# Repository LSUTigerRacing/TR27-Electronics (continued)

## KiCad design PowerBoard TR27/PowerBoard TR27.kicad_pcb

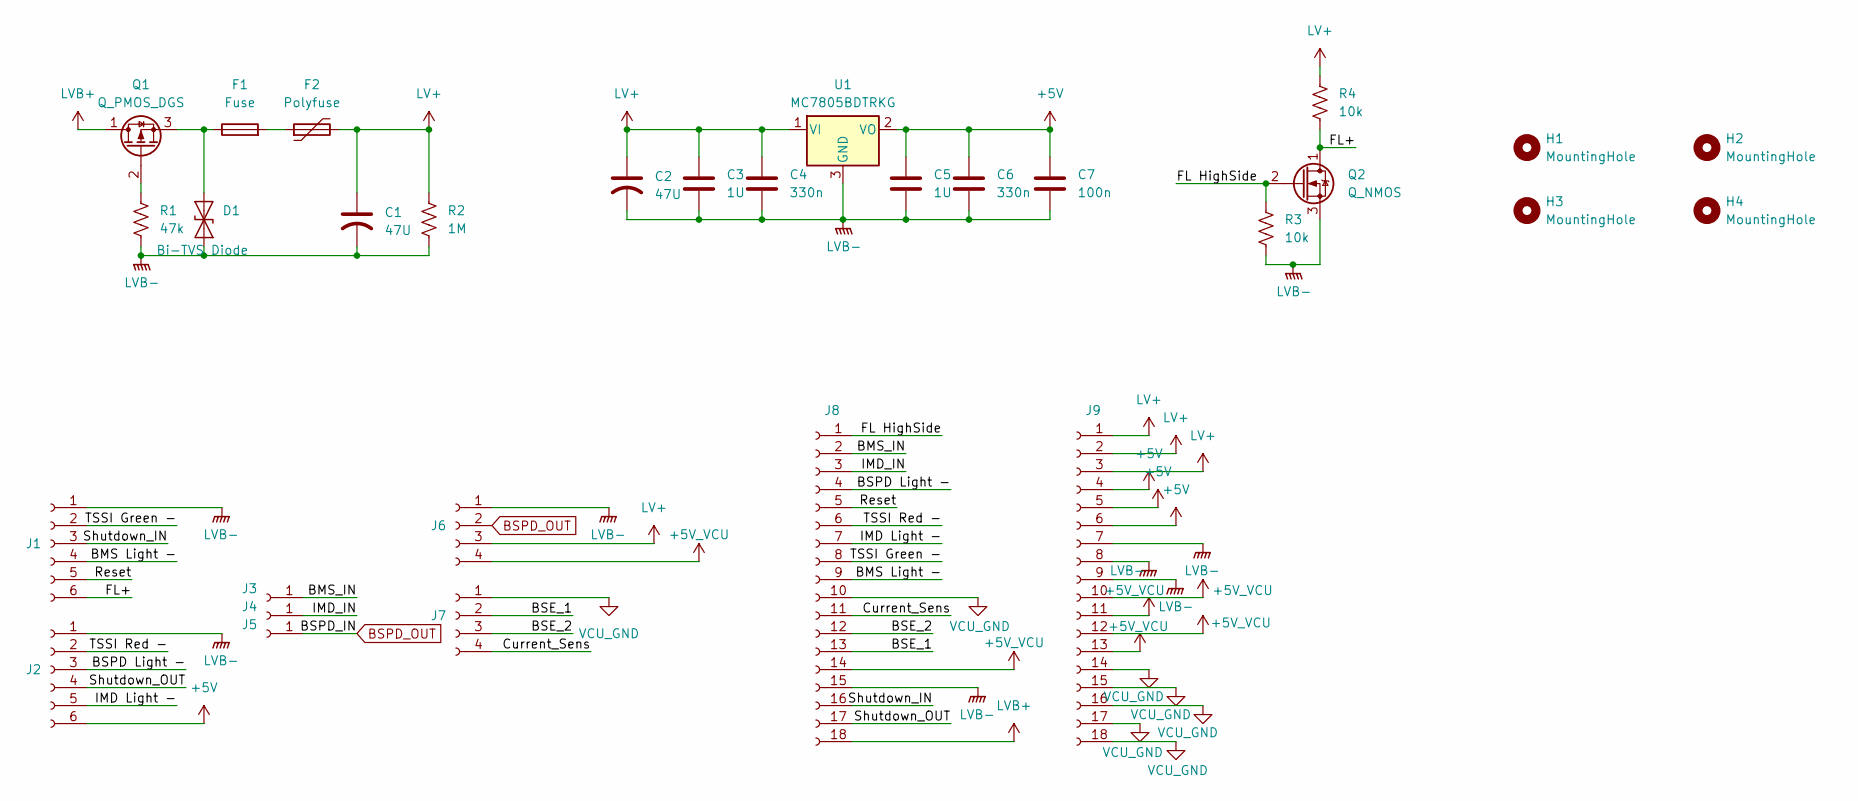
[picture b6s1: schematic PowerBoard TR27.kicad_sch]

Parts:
C1, C2: 47U; CP_Elec_6.3x5.4; JLC# C2836440
C3, C5: 1U; C_0603_1608Metric
C4, C6: 330n; C_0603_1608Metric
C7: 100n; C_0603_1608Metric
D1: Bi-TVS Diode; D_SOD-523; Mouser# 750-CPDUR12V-HF; JLC# C2443698
F1: Fuse; Fuseholder_Blade_Mini_Keystone_3568
F2: Polyfuse; R_0805_2012Metric
H1, H2, H3, H4: MountingHole; MountingHole_3.2mm_M3_DIN965_Pad
J1, J2: Conn_01x06_Socket; SAMTEC-CES-103-01-X-D
J3, J4, J5: Conn_01x01_Socket; SAMTEC_CES-101-01-T-S
J6, J7: Conn_01x04_Socket; SAMTEC_CES-104-X-X-S
J8, J9: Conn_01x18_Socket; CONN_SD-43045-001_18_MOL
Q1: Q_PMOS_DGS; SOT-23-3
Q2: Q_NMOS; SOT-23-3
R1: 47k; R_0805_2012Metric
R2: 1M; R_0805_2012Metric
R3, R4: 10k; R_0805_2012Metric
U1: MC7805BDTRKG; TO-252-3_TabPin2

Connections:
+5V: C5.1, C6.1, C7.1, J2.6, J9.4, J9.5, J9.6, U1.2 (VO)
+5V_VCU: J6.4, J8.14, J9.10, J9.11, J9.12, J9.13
/BMS Light -: J1.4, J8.9
/BMS_IN: J3.1 (Pin_1_1), J8.2
/BSE_1: J7.2, J8.13
/BSE_2: J7.3, J8.12
/BSPD Light -: J2.3, J8.4
/Current_Sens: J7.4, J8.11
/FL HighSide: J8.1, Q2.2 (G), R3.1
/FL+: J1.6, Q2.1 (D), R4.2
/IMD Light -: J2.5, J8.7
/IMD_IN: J4.1 (Pin_1_1), J8.3
/Reset: J1.5, J8.5
/Shutdown_IN: J1.3, J8.16
/Shutdown_OUT: J2.4, J8.17
/TSSI Green -: J1.2, J8.8
/TSSI Red -: J2.2, J8.6
BSPD_OUT: J5.1 (Pin_1_1), J6.2
LV+: C1.1, C2.1, C3.1, C4.1, F2.2, J6.3, J9.1, J9.2, J9.3, R2.1, R4.1, U1.1 (VI)
LVB+: J8.18, Q1.1 (D)
LVB-: C1.2, C2.2, C3.2, C4.2, C5.2, C6.2, C7.2, D1.1 (A1), J1.1, J2.1, J6.1, J8.15, J9.7, J9.8, J9.9, Q2.3 (S), R1.2, R2.2, R3.2, U1.3 (GND)
unnamed: D1.2 (A2), F1.1, Q1.3 (S)
unnamed: F1.2, F2.1
unnamed: Q1.2 (G), R1.1
VCU_GND: J7.1, J8.10, J9.14, J9.15, J9.16, J9.17, J9.18

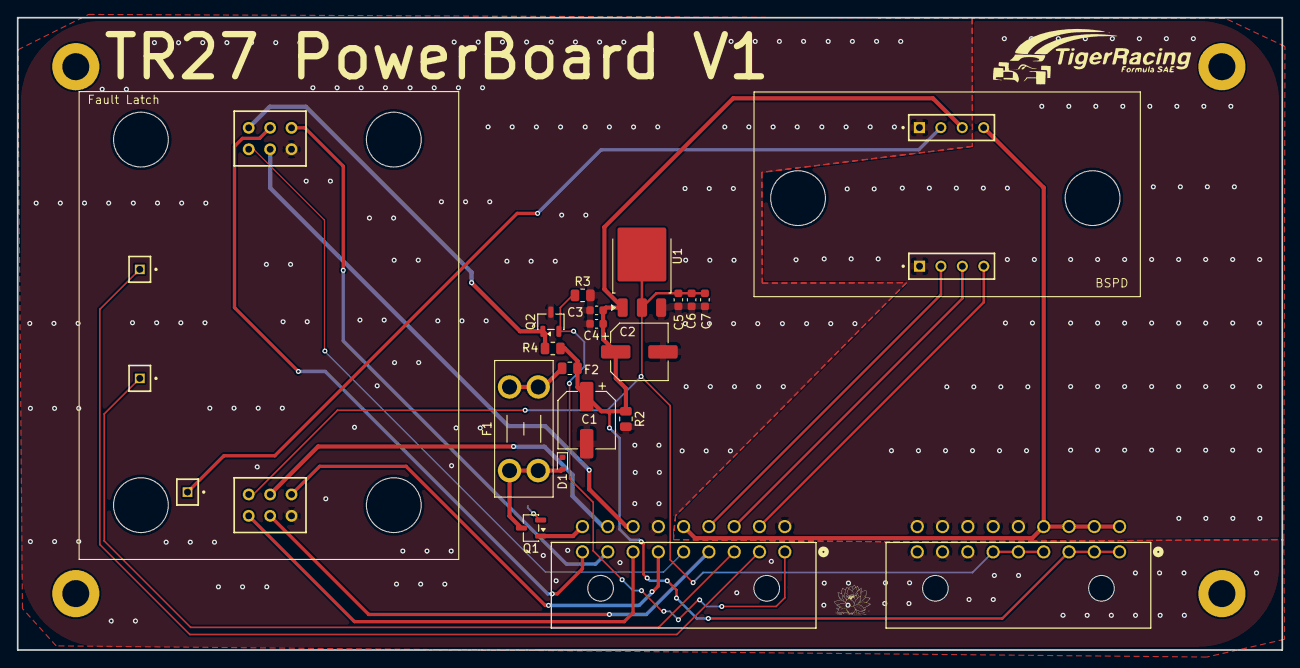
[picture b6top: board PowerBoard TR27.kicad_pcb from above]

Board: 2 copper layers, 150.0 x 75.0 mm, 30 parts (1 on the bottom side), 25 nets.

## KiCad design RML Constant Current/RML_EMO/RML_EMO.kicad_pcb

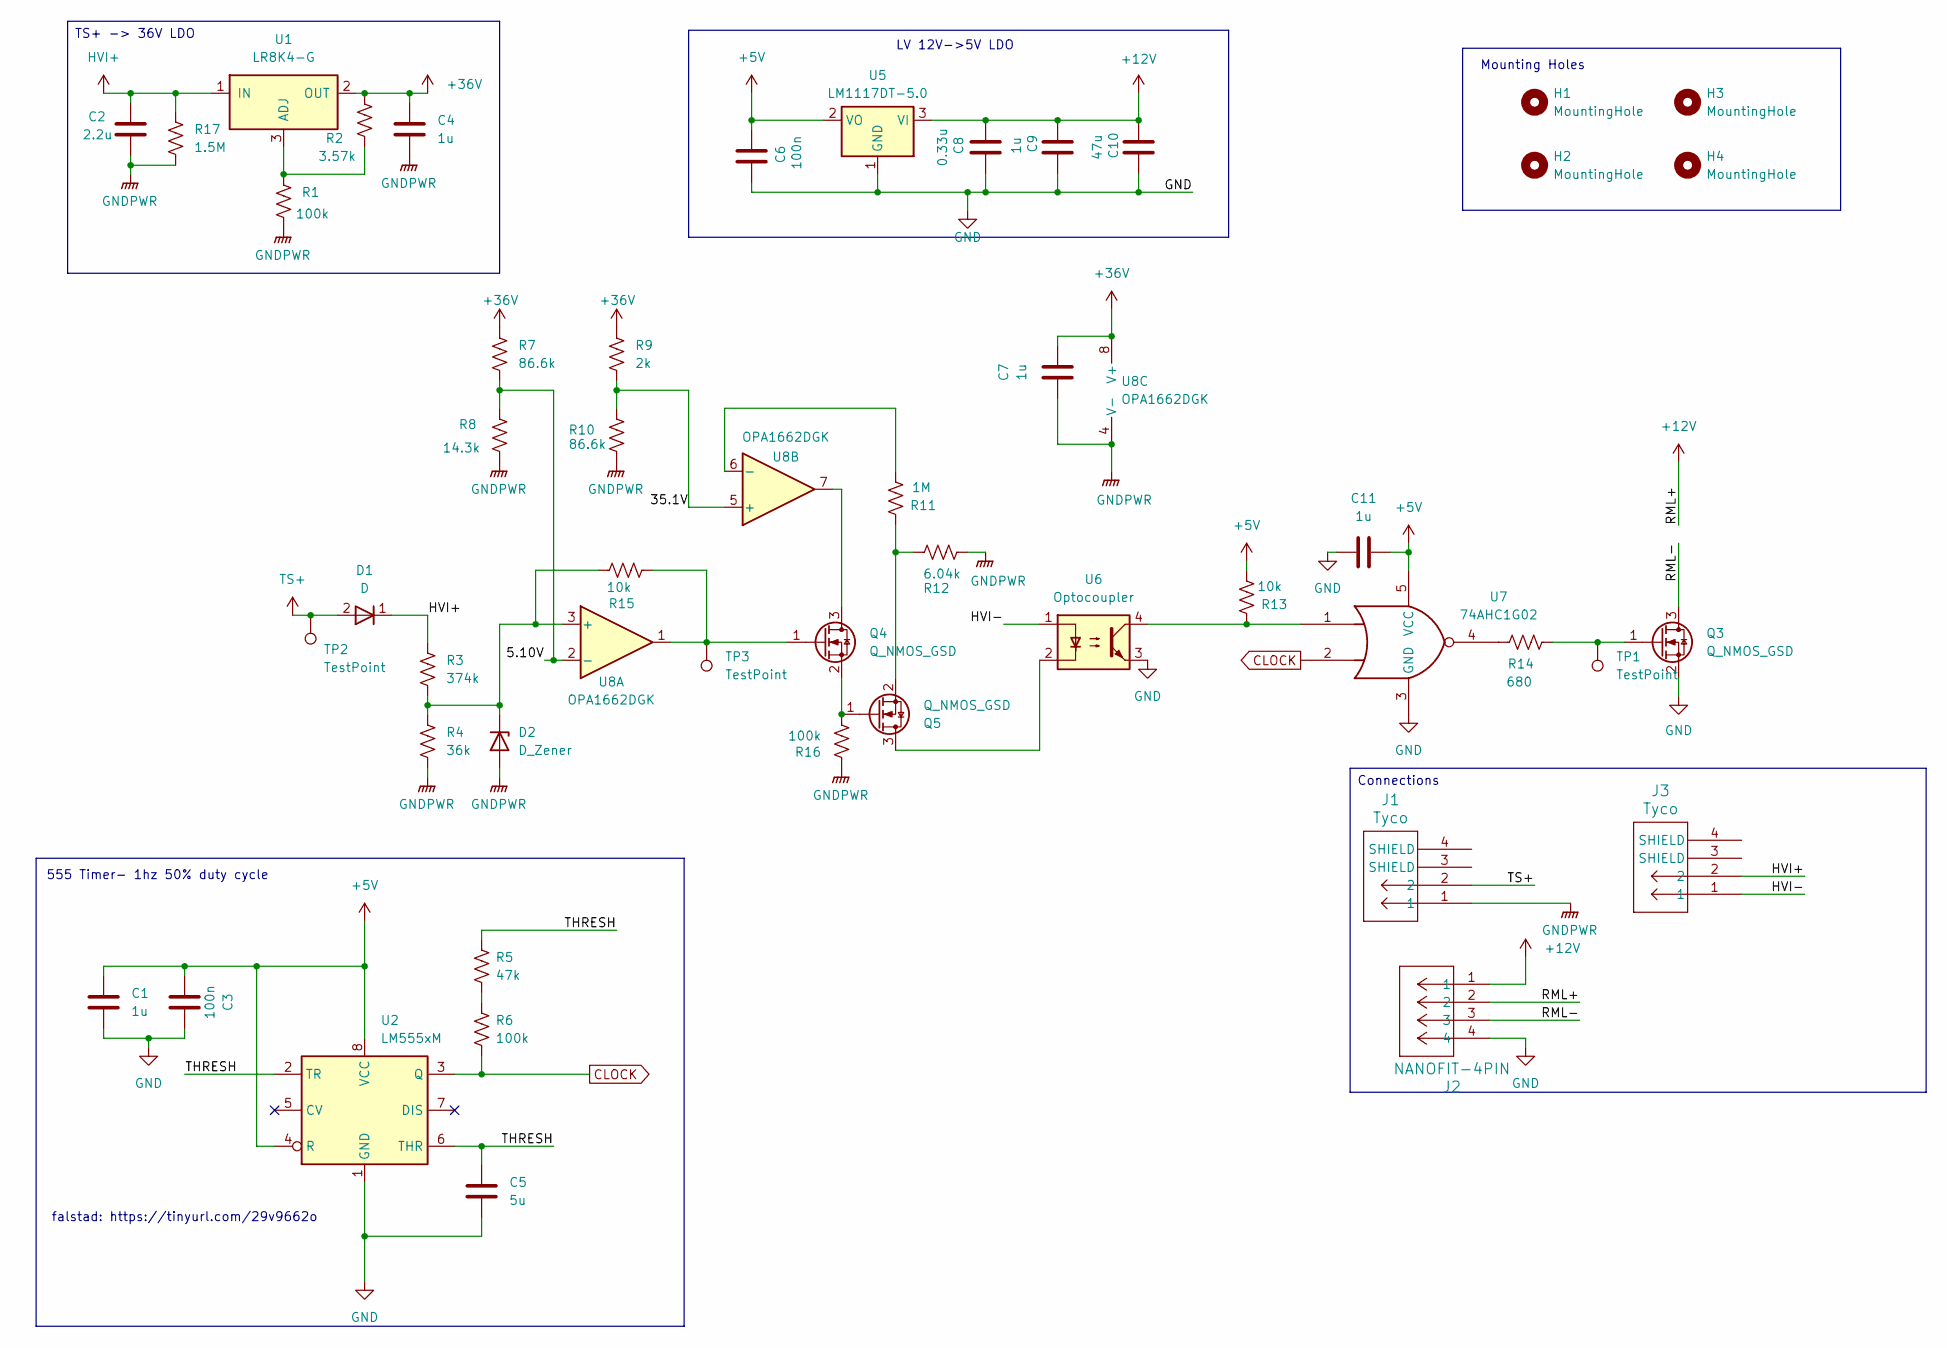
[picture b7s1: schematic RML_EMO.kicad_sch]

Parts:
C1: 1u; C_0603_1608Metric; Mouser# 603-AC0805KKX7R9B105
C2: 2.2u; CAP_6050_TDK; Manufacturer# CAA572X6T2W225M640LJ; Digikey# 445-CAA572X6T2W225M640LJCT-ND
C3: 100n; C_0603_1608Metric; Mouser# 603-AC0603KR9BB104
C4, C7, C9, C11: 1u; C_0805_2012Metric_Pad1.18x1.45mm_HandSolder; Mouser# 603-AC0805KKX7R9B105
C5: 5u; C_0603_1608Metric; Mouser# 963-MLASG168BB5475KT
C6: 100n; C_0603_1608Metric_Pad1.08x0.95mm_HandSolder; Mouser# 603-AC0603KR9BB104
C8: 0.33u; C_0603_1608Metric_Pad1.08x0.95mm_HandSolder; Manufacturer# CC0603KRX7R6BB334; JLC# C282682
C10: 47u; CP_Elec_6.3x5.4; JLC# C2836440
D1: D; D_SOD-523; Mouser# 755-RFU01SM4ST2R
D2: D_Zener; Nexperia_CFP3_SOD-123W; Manufacturer# MMSZ5240C-HE3_A-08; Mouser# 78-MMSZ5240CHE3_A-08
H1, H2, H3, H4: MountingHole; MountingHole_3.2mm_M3_DIN965_Pad_TopOnly
J1, J3: Tyco; tyco
J2: NANOFIT-4PIN; Molex_Nano-Fit_105313-xx04_1x04_P2.50mm_Horizontal
Q3: Q_NMOS_GSD; SOT-23; JLC# C2590
Q4: Q_NMOS_GSD; SOT-23; Digikey# 5318-AM2398N-ND
Q5: Q_NMOS_GSD; TO-220-3_Vertical; Digikey# IPP60R180P7XKSA1-ND
R1, R16: 100k; R_0805_2012Metric_Pad1.20x1.40mm_HandSolder; Manufacturer# RC0805FR-10100KL; Digikey# 13-RC0805FR-10100KLCT-ND
R2: 3.57k; R_0805_2012Metric_Pad1.20x1.40mm_HandSolder; Mouser# 652-CR0805FX-3571ELF
R3: 374k; R_0805_2012Metric; Mouser# 71-CRCW0805374KFKEA
R4: 36k; R_0805_2012Metric_Pad1.20x1.40mm_HandSolder; Mouser# 667-ERJ-P06F3602V
R5: 47k; R_1206_3216Metric; Manufacturer# RC1206FR-0747KL; JLC# C25664
R6: 100k; R_1206_3216Metric; Manufacturer# RC1206FR-07100KL; JLC# C17900
R7, R10: 86.6k; R_0805_2012Metric_Pad1.20x1.40mm_HandSolder; Mouser# 667-ERJ-P06F8662V
R8: 14.3k; R_0805_2012Metric_Pad1.20x1.40mm_HandSolder; Mouser# 667-ERJ-P06F1432V
R9: 2k; R_0805_2012Metric_Pad1.20x1.40mm_HandSolder; Mouser# 71-CRCW08052K00JNEA
R11: 1M; R_0805_2012Metric_Pad1.20x1.40mm_HandSolder; Mouser# 667-ERJ-P06J105V
R12: 6.04k; R_0805_2012Metric_Pad1.20x1.40mm_HandSolder; Mouser# 667-ERJ-P06F6041V
R13, R15: 10k; R_0805_2012Metric_Pad1.20x1.40mm_HandSolder; Manufacturer# 311-10.0KCRCT-ND; Digikey# 603-RC0805FR-0710KL
R14: 680; R_0805_2012Metric_Pad1.20x1.40mm_HandSolder; Mouser# 603-RC0805FR-07680RL
R17: 1.5M; R_2010_5025Metric_Pad1.40x2.65mm_HandSolder; Mouser# 603-RC2010JK-071M5L
TP1, TP2, TP3: TestPoint; TestPoint_Pad_1.0x1.0mm
U1: LR8K4-G; TO-252-2; Manufacturer# LR8K4-G; Digikey# LR8K4-GCT-ND
U2: LM555xM; SOIC-8_3.9x4.9mm_P1.27mm; Manufacturer# LMC555CMX/NOPBCT-ND; JLC# C90760
U5: LM1117DT-5.0; TO-252-3_TabPin2; Manufacturer# LM1117DT-5.0/NOPB; JLC# C354068
U6: Optocoupler; Q_Wurth_WL-OCPT_LSOP4-STANDARD; Mouser# 78-VOLA617A-3X001T
U7: 74AHC1G02; SOT-353_SC-70-5; Mouser# 595-SN74AHC1G02DCG4
U8: OPA1662DGK; VSSOP-8_3x3mm_P0.65mm; Mouser# OPA1662DGK

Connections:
+5V: C1.1, C3.1, C6.2, C11.1, R13.1, U2.4 (R), U2.8 (VCC), U5.2 (VO), U7.5 (VCC)
+12V: C8.1, C9.1, C10.1, J2.1, J2.2, U5.3 (VI)
+36V: C4.1, C7.1, R2.2, R7.2, R9.2, U1.2 (OUT), U8.8 (V+)
/5.10V: R7.1, R8.2, U8.2 (-)
/35.1V: R9.1, R10.2, U8.5 (+)
/HVI-: J3.1, U6.1
/RML-: J2.3, Q3.3 (D)
/THRESH: C5.1, R5.1, U2.2 (TR), U2.6 (THR)
CLOCK: R6.2, U2.3 (Q), U7.2
GND: C1.2, C3.2, C5.2, C6.1, C8.2, C9.2, C10.2, C11.2, J2.4, Q3.2 (S), U2.1 (GND), U5.1 (GND), U6.3, U7.3 (GND)
GNDPWR: C2.2, C4.2, C7.2, D2.2 (A), J1.1, R1.1, R4.2, R8.1, R10.1, R12.2, R16.2, R17.1, U8.4 (V-)
HVI+: C2.1, D1.1 (K), J3.2, R3.1, R17.2, U1.1 (IN)
unnamed: D2.1 (K), R3.2, R4.1, R15.2, U8.3 (+)
unnamed: Q3.1 (G), R14.1, TP1.1 (1_1)
unnamed: Q4.3 (D), U8.7
unnamed: Q4.1 (G), R15.1, TP3.1 (1_1), U8.1
unnamed: Q4.2 (S), Q5.1 (G), R16.1
unnamed: Q5.3 (D), U6.2
unnamed: Q5.2 (S), R11.2, R12.1
unnamed: R5.2, R6.1
unnamed: R13.2, U6.4, U7.1
unnamed: R14.2, U7.4
unnamed: R1.2, R2.1, U1.3 (ADJ)
unnamed: R11.1, U8.6 (-)
TS+: D1.2 (A), J1.2, TP2.1 (1_1)

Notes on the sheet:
Mounting Holes
555 Timer- 1hz 50% duty cycle
LV 12V->5V LDO
falstad: https://tinyurl.com/29v9662o
TS+ -> 36V LDO
Connections

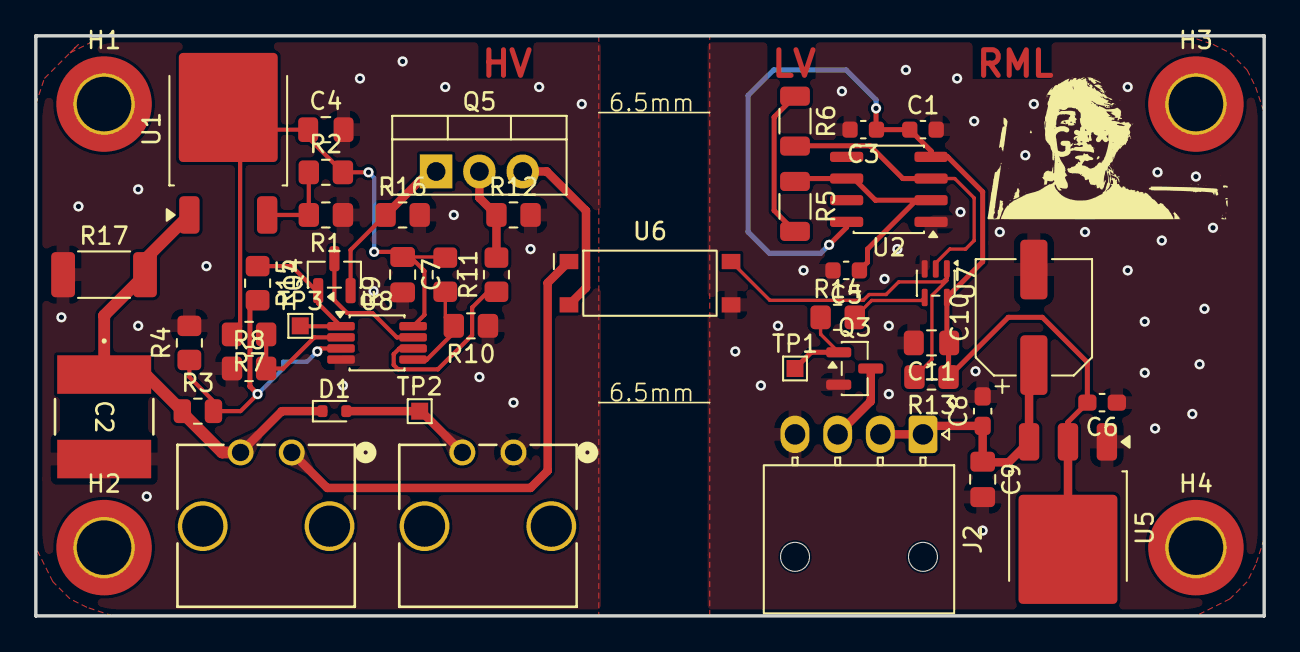
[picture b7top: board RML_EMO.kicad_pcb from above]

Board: 2 copper layers, 72.0 x 34.0 mm, 49 parts (1 on the bottom side), 25 nets.
